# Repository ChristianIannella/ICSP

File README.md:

# ICSP
[Buy on Tindie](https://www.tindie.com/products/chris_maker_/attiny85-uploader/)

<picture><picture>

Con questo shield è possibile caricare il bootloader Arduino su microcontrollori come l'Atmega329P (Arduino Uno) o quelli della famiglia Attiny, è anche possibile
caricare il tuo sketch senza bisogno di interfaccia USB/UART.
Lo shield dispone di zoccolo per programmare un Attiny85 DIP, a bordo sono presenti tre led di segnalazione: **Power**, **Programming** e **Error**. 

Prima di tutto dovrai caricare su una scheda Arduino UNO lo sketch **ArduinoISP** che trovi nella sezione **Esempi** 

Ecco il pinout della porta ICSP e il pinout di alcuni uC.

# ATMEGA328P

- Avvia l'IDE Arduino
- Dal menu **Strumenti** seleziona la scheda **Arduino Nano** o **Arduino Uno**
- Dal menu **Strumenti** seleziona **Programmatore** **ArduinoISP**
- Ora dovrai scrivere il bootloader dal menu **Strumenti** e cliccando su **Scrivi il bootloader**
- Fatto questo non ti resta che caricare il tuo sketch dal menu **Sketch** cliccando su **Carica tramite programmatore**

# ATTINY85

- Avvia l'IDE Arduino
- Vai in **Impostazioni** e aggiungi il seguente URL nell'apposito spazio: 
https://raw.githubusercontent.com/damellis/attiny/ide-1.6.x-boards-manager/package_damellis_attiny_index.json
- Dal **Gestore schede** cerca "Attiny" e installa i files.
- Dal menu **Strumenti** seleziona la scheda **Attiny25/45/85**
- Dal menu **Strumenti** seleziona **Programmatore** **ArduinoISP**
- Ora dovrai scrivere il bootloader dal menu **Strumenti** e cliccando su **Scrivi il bootloader**
- Fatto questo non ti resta che caricare il tuo sketch dal menu **Sketch** cliccando su **Carica tramite programmatore**

Provalo con [Dice keychain](https://www.tindie.com/products/chris_maker_/attiny85-keychain-dice/)

# Contribute
Please, feel free to contribute.

# Author
Iannella Christian

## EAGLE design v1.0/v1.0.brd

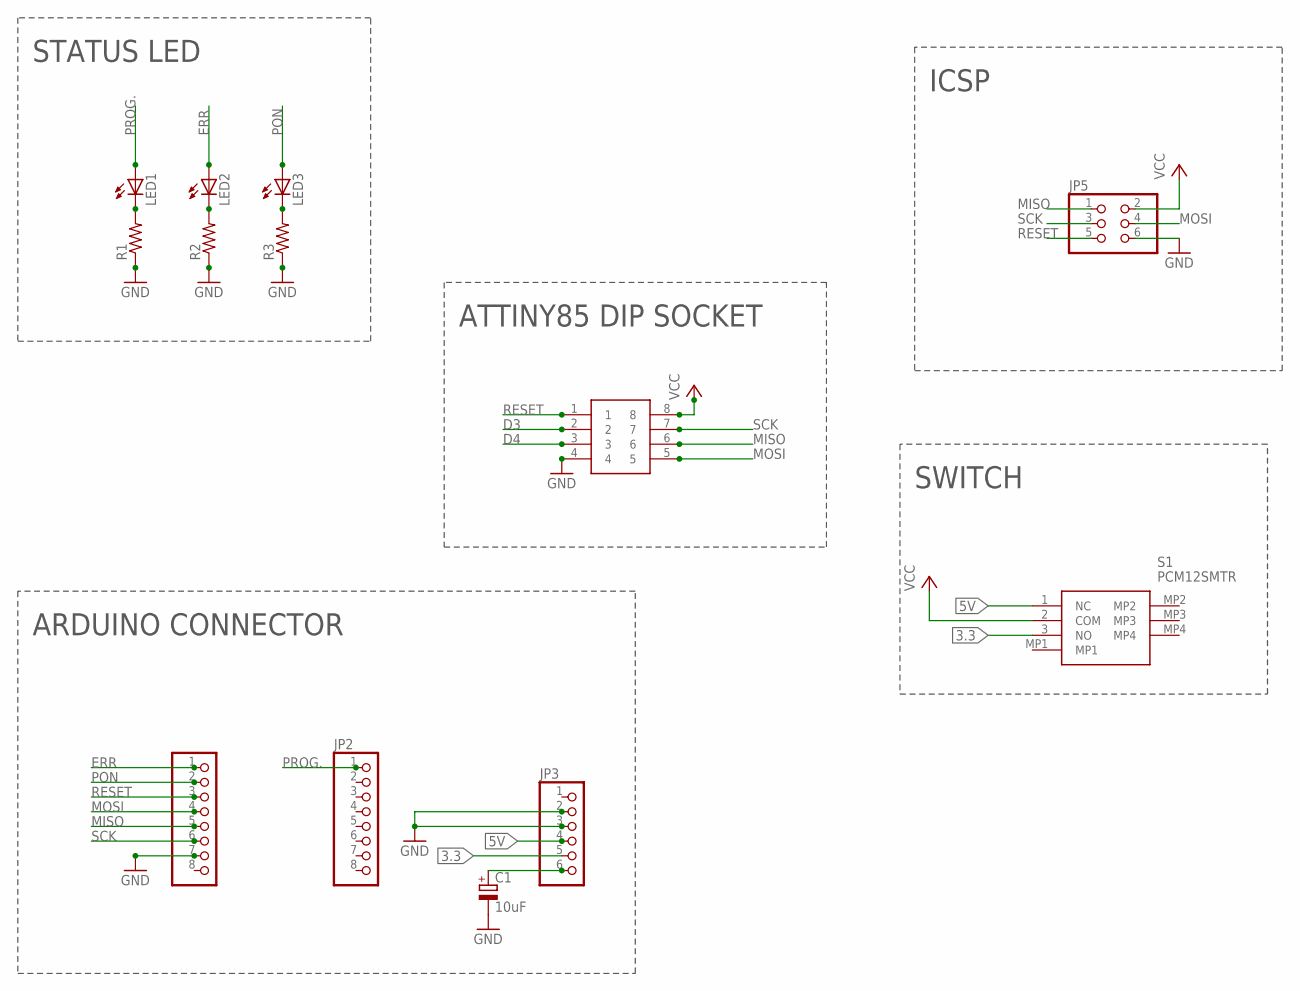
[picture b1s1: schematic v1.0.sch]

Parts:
C1: 10uF; E2-5
IC1: 1-2199298-2; DIPS762W70P254L1016H510Q8N
JP2, JP4: PINHD-1X8; 1X08
JP3: PINHD-1X6; 1X06
JP5: PINHD-2X3; 2X03
LED1, LED2, LED3: LED3MM
R1, R2, R3: R-US_0207/10; 0207/10
S1: PCM12SMTR

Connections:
3.3: JP3.5, S1.3 (NO)
5V: JP3.4, S1.1 (NC)
D3: IC1.2
D4: IC1.3
ERR: JP4.1, LED2.A
GND: C1.-, IC1.4, JP3.2, JP3.3, JP4.7, JP5.6, R1.1, R2.1, R3.1
MISO: IC1.6, JP4.5, JP5.1
MOSI: IC1.5, JP4.4, JP5.4
unnamed: C1.+, JP3.6
unnamed: LED1.K (C), R1.2
unnamed: LED2.K (C), R2.2
unnamed: LED3.K (C), R3.2
PON: JP4.2, LED3.A
PROG.: JP2.1, LED1.A
RESET: IC1.1, JP4.3, JP5.5
SCK: IC1.7, JP4.6, JP5.3
VCC: IC1.8, JP5.2, S1.2 (COM)

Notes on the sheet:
STATUS LED
ARDUINO CONNECTOR
ATTINY85 DIP SOCKET
ICSP
SWITCH

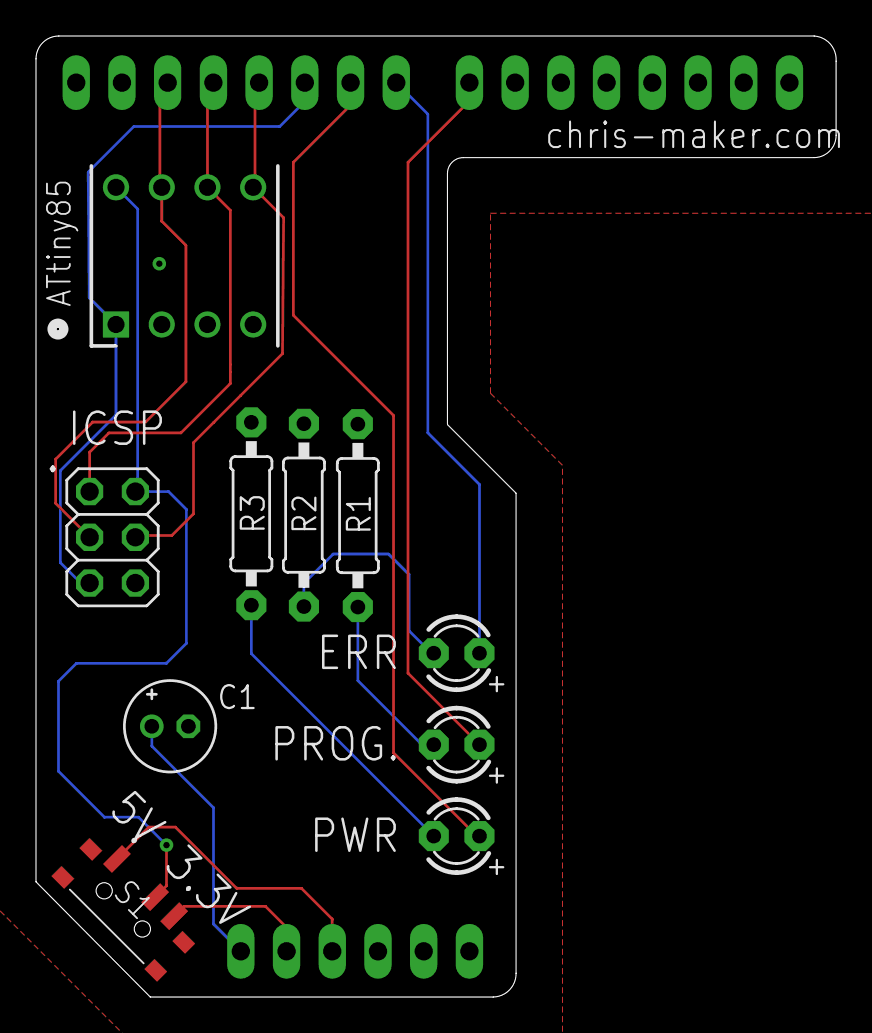
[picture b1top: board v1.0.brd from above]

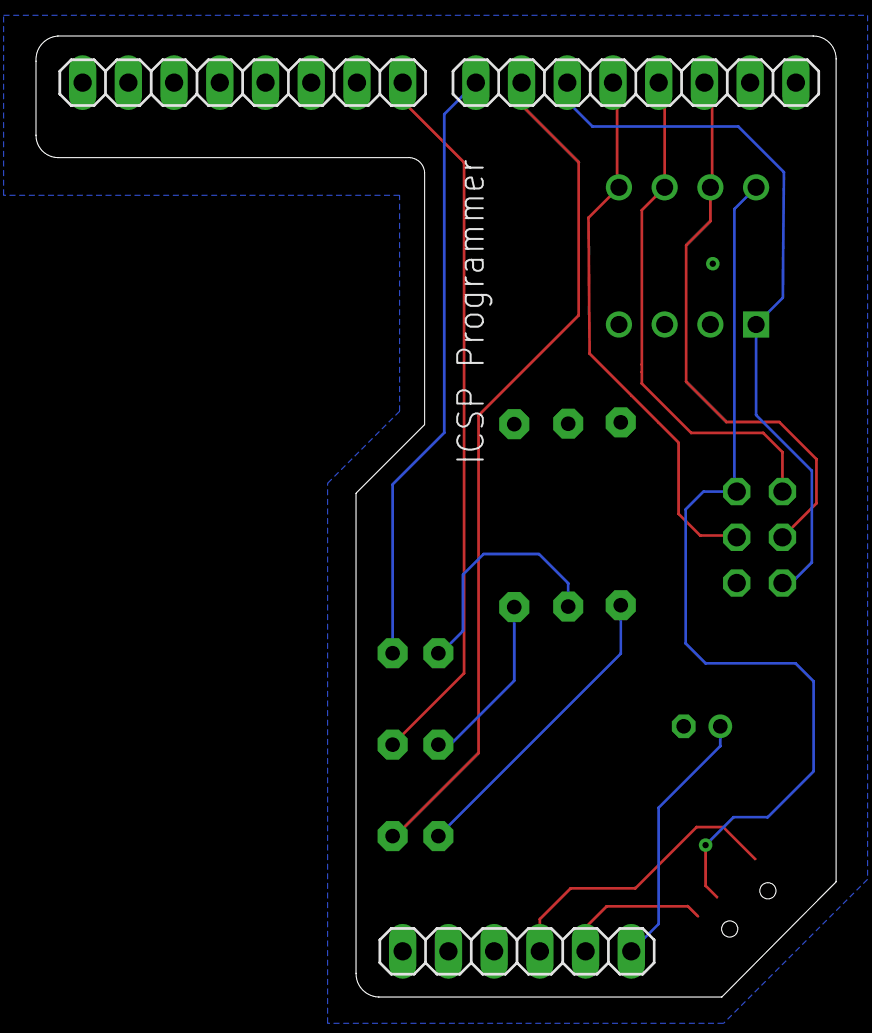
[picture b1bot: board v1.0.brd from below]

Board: 2 copper layers, 44.5 x 53.4 mm, 13 parts (3 on the bottom side), 15 nets.

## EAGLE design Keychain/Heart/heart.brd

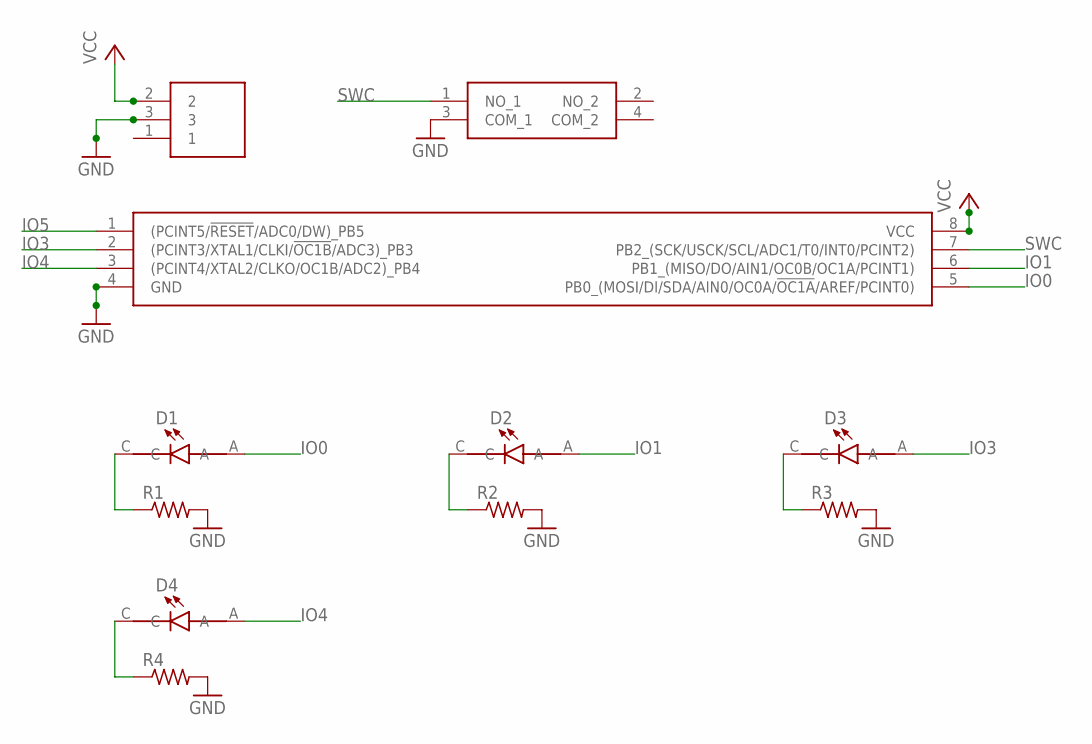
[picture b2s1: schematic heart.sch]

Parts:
D1, D2, D3, D4: SML-LXT0805IW-TR; LEDC2012X120N
IC1: ATTINY85-20SU; SOIC127P798X216-8N
R1, R2, R3, R4: R-US_R0805; R0805
S1: TS18-5-20-SL-160-SMT-TR; TS18520SL160SMTTR
U1: BAT-HLD-001; BATHLD001

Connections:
GND: IC1.4 (GND), R1.2, R2.2, R3.2, R4.2, S1.3 (COM_1), U1.3
IO0: D1.A, IC1.5 (PB0_(MOSI/DI/SDA/AIN0/OC0A/!OC1A!/AREF/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)
IO1: D2.A, IC1.6 (PB1_(MISO/DO/AIN1/OC0B/OC1A/PCINT1))
IO3: D3.A, IC1.2 ((PCINT3/XTAL1/CLKI/!OC1B!/ADC3)_PB3)
IO4: D4.A, IC1.3 ((PCINT4/XTAL2/CLKO/OC1B/ADC2)_PB4)
IO5: IC1.1 ((PCINT5/!RESET!/ADC0/DW)_PB5)
unnamed: D1.C, R1.1
unnamed: D4.C, R4.1
unnamed: D2.C, R2.1
unnamed: D3.C, R3.1
SWC: IC1.7 (PB2_(SCK/USCK/SCL/ADC1/T0/INT0/PCINT2)), S1.1 (NO_1)
VCC: IC1.8 (VCC), U1.2

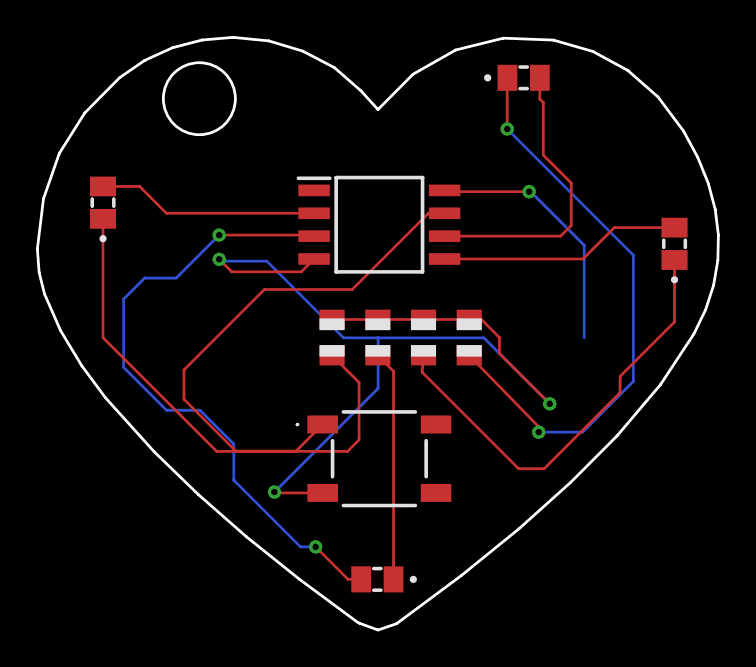
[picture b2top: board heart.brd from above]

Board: 2 copper layers, 37.8 x 32.9 mm, 11 parts (1 on the bottom side), 11 nets.

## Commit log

2023-07-18 Upload docs
2023-09-28 Create LICENSE
2023-10-11 Upload
